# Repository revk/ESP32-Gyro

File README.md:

# ESP32-Gyro

Now at [Codeberg](https://codeberg.org/RevK/ESP32-Gyro)

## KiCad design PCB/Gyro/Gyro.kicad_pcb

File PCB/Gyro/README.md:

# Gyro

These files are for use in [KiCad](https://www.kicad.org).

## Trademark

This is an open source project, but bear in mind you cannot sell boards bearing the Andrews & Arnold Ltd name, the A&A logo, the registered trademark AJK logo, or the GS1 allocated EANs assigned to Andrews & Arnold Ltd.

## Images

*Auto generated 2025-07-08T09:44:21*

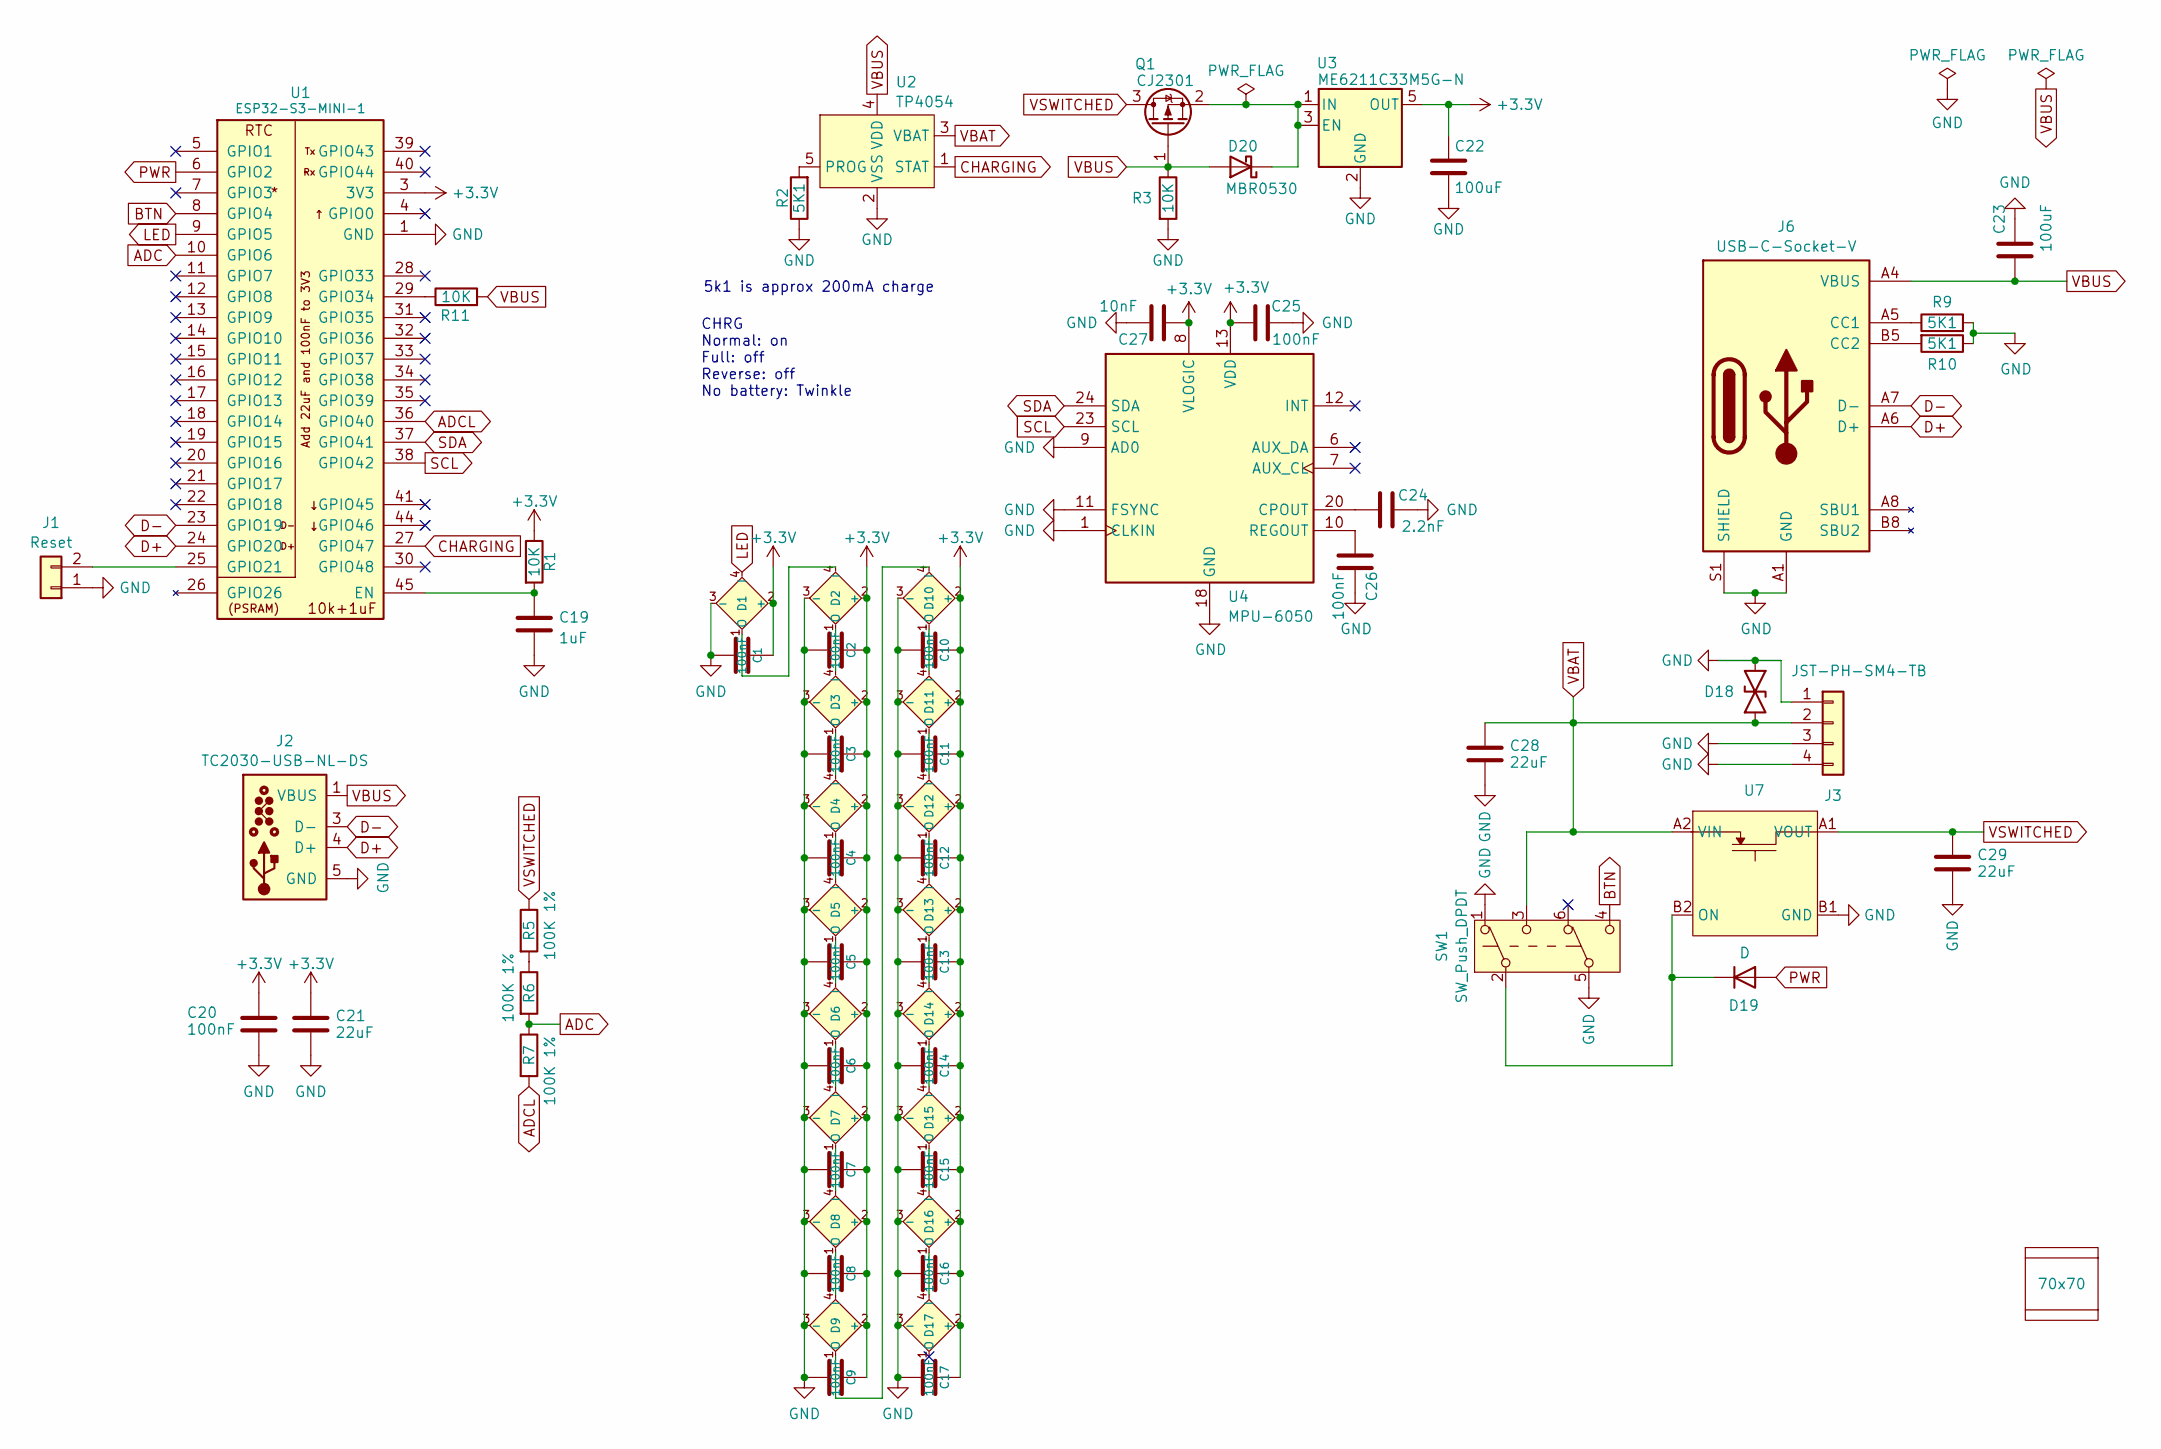
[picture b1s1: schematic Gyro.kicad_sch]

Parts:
C1, C2, C3, C4, C5, C6, C7, C8, C9, C10, C11, C12, C13, C14, C15, C16, C17, C20, C25, C26: 100nF; C_0402
C19: 1uF; C_0402
C21, C28, C29: 22uF; C_0603
C22, C23: 100uF; C_0805; MPN C141660
C24: 2.2nF; C_0402
C27: 10nF; C_0402
D1, D2, D3, D4, D5, D6, D7, D8, D9, D10, D11, D12, D13, D14, D15, D16, D17: XL-1010RGBC-WS2812B; SMD1010; MPN C5349953
D18: DFN1006-2L; MPN C5137770
D19: D; D_0402; MPN C28642302
D20: MBR0530; D_SOD-123; MPN C5204746
J1: Reset; AA-Pad
J2: TC2030-USB-NL-DS; Tag-Connect_TC2030-IDC-NL_2x03_P1.27mm_Vertical
J3: JST-PH-SM4-TB; JST_PH_S2B-PH-SM4-TB_1x02-1MP_P2.00mm_Horizontal; MPN C295747
J6: USB-C-Socket-V; USB-C-Socket-H; MPN C709357
PCB1: 70x70; PCB7070
Q1: CJ2301; SOT-23; MPN C8547
R1, R3, R11: 10K; R_0402; MPN C25744
R2, R9, R10: 5K1; R_0402; MPN C25905
R5, R6, R7: 100K 1%; R_0402; MPN C5139597
SW1: SW_Push_DPDT; MPN C2911139
U1: ESP32-S3-MINI-1; MPN C3013941
U2: TP4054; SOT-23-5; MPN C668215
U3: ME6211C33M5G-N; SOT-23-5; MPN C82942
U4: MPU-6050; InvenSense_QFN-24_4x4mm_P0.5mm; MPN C24112
U7: WCSP-4-0.78x0.78; MPN C2655476
V1, V2: VCUT70N

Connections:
+3.3V: C1.1, C2.1, C3.1, C4.1, C5.1, C6.1, C7.1, C8.1, C9.1, C10.1, C11.1, C12.1, C13.1, C14.1, C15.1, C16.1, C17.1, C20.1, C21.1, C22.1, C25.1, C27.1, D1.2 (+), D2.2 (+), D3.2 (+), D4.2 (+), D5.2 (+), D6.2 (+), D7.2 (+), D8.2 (+), D9.2 (+), D10.2 (+), D11.2 (+), D12.2 (+), D13.2 (+), D14.2 (+), D15.2 (+), D16.2 (+), D17.2 (+), R1.1, U1.3 (3V3), U3.5 (OUT), U4.8 (VLOGIC), U4.13 (VDD)
ADC: R6.2, R7.1, U1.10 (GPIO6)
ADCL: R7.2, U1.36 (GPIO40)
BTN: SW1.4 (C), U1.8 (GPIO4)
CHARGING: U1.27 (GPIO47), U2.1 (STAT)
D+: J2.4 (D+), J6.A6 (D+), J6.B6 (D+), U1.24 (GPIO20)
D-: J2.2 (NC), J2.3 (D-), J2.6 (NC), J6.A7 (D-), J6.B7 (D-), U1.23 (GPIO19)
GND: C1.2, C2.2, C3.2, C4.2, C5.2, C6.2, C7.2, C8.2, C9.2, C10.2, C11.2, C12.2, C13.2, C14.2, C15.2, C16.2, C17.2, C19.2, C20.2, C21.2, C22.2, C23.2, C24.2, C25.2, C26.2, C27.2, C28.2, C29.2, D1.3 (-), D2.3 (-), D3.3 (-), D4.3 (-), D5.3 (-), D6.3 (-), D7.3 (-), D8.3 (-), D9.3 (-), D10.3 (-), D11.3 (-), D12.3 (-), D13.3 (-), D14.3 (-), D15.3 (-), D16.3 (-), D17.3 (-), D18.1, J1.1, J2.5 (GND), J3.1, J3.3, J3.4, J6.A1 (GND), J6.A12 (GND), J6.B1 (GND), J6.B12 (GND), J6.S1 (SHIELD), R2.1, R3.2, R9.2, R10.1, SW1.1 (A), SW1.5 (B), U1.1 (GND), U1.2 (GND), U1.42 (GND), U1.43 (GND), U1.46 (GND), U1.47 (GND), U1.48 (GND), U1.49 (GND), U1.50 (GND), U1.51 (GND), U1.52 (GND), U1.53 (GND), U1.54 (GND), U1.55 (GND), U1.56 (GND), U1.57 (GND), U1.58 (GND), U1.59 (GND), U1.60 (GND), U1.61 (GND), U1.62 (GND), U1.63 (GND), U1.64 (GND), U1.65 (GND), U2.2 (VSS), U3.2 (GND), U4.1 (CLKIN), U4.9 (AD0), U4.11 (FSYNC), U4.18 (GND), U7.B1 (GND)
LED: D1.4 (I), U1.9 (GPIO5)
unnamed: D1.1 (O), D2.4 (I)
unnamed: D2.1 (O), D3.4 (I)
unnamed: D3.1 (O), D4.4 (I)
unnamed: D4.1 (O), D5.4 (I)
unnamed: D5.1 (O), D6.4 (I)
unnamed: D6.1 (O), D7.4 (I)
unnamed: D7.1 (O), D8.4 (I)
unnamed: D8.1 (O), D9.4 (I)
unnamed: D9.1 (O), D10.4 (I)
unnamed: D10.1 (O), D11.4 (I)
unnamed: D11.1 (O), D12.4 (I)
unnamed: D12.1 (O), D13.4 (I)
unnamed: D13.1 (O), D14.4 (I)
unnamed: D14.1 (O), D15.4 (I)
unnamed: D15.1 (O), D16.4 (I)
unnamed: D16.1 (O), D17.4 (I)
unnamed: D19.1 (K), SW1.2 (B), U7.B2 (ON)
unnamed: D20.1 (K), Q1.2 (S), U3.1 (IN), U3.3 (EN)
unnamed: J1.2, U1.25 (GPIO21)
unnamed: J6.A5 (CC1), R9.1
unnamed: J6.B5 (CC2), R10.2
unnamed: R5.2, R6.1
unnamed: C19.1, R1.2, U1.45 (EN)
unnamed: R11.1, U1.29 (GPIO34)
unnamed: R2.2, U2.5 (PROG)
unnamed: C24.1, U4.20 (CPOUT)
unnamed: C26.1, U4.10 (REGOUT)
PWR: D19.2 (A), U1.6 (GPIO2)
SCL: U1.38 (GPIO42), U4.23 (SCL)
SDA: U1.37 (GPIO41), U4.24 (SDA)
VBAT: C28.1, D18.2, J3.2, SW1.3 (C), U2.3 (VBAT), U7.A2 (VIN)
VBUS: C23.1, D20.2 (A), J2.1 (VBUS), J6.A4 (VBUS), J6.A9 (VBUS), J6.B4 (VBUS), J6.B9 (VBUS), Q1.1 (G), R3.1, R11.2, U2.4 (VDD)
VSWITCHED: C29.1, Q1.3 (D), R5.1, U7.A1 (VOUT)

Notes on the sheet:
5k1 is approx 200mA charge
CHRG Normal: on Full: off Reverse: off No battery: Twinkle

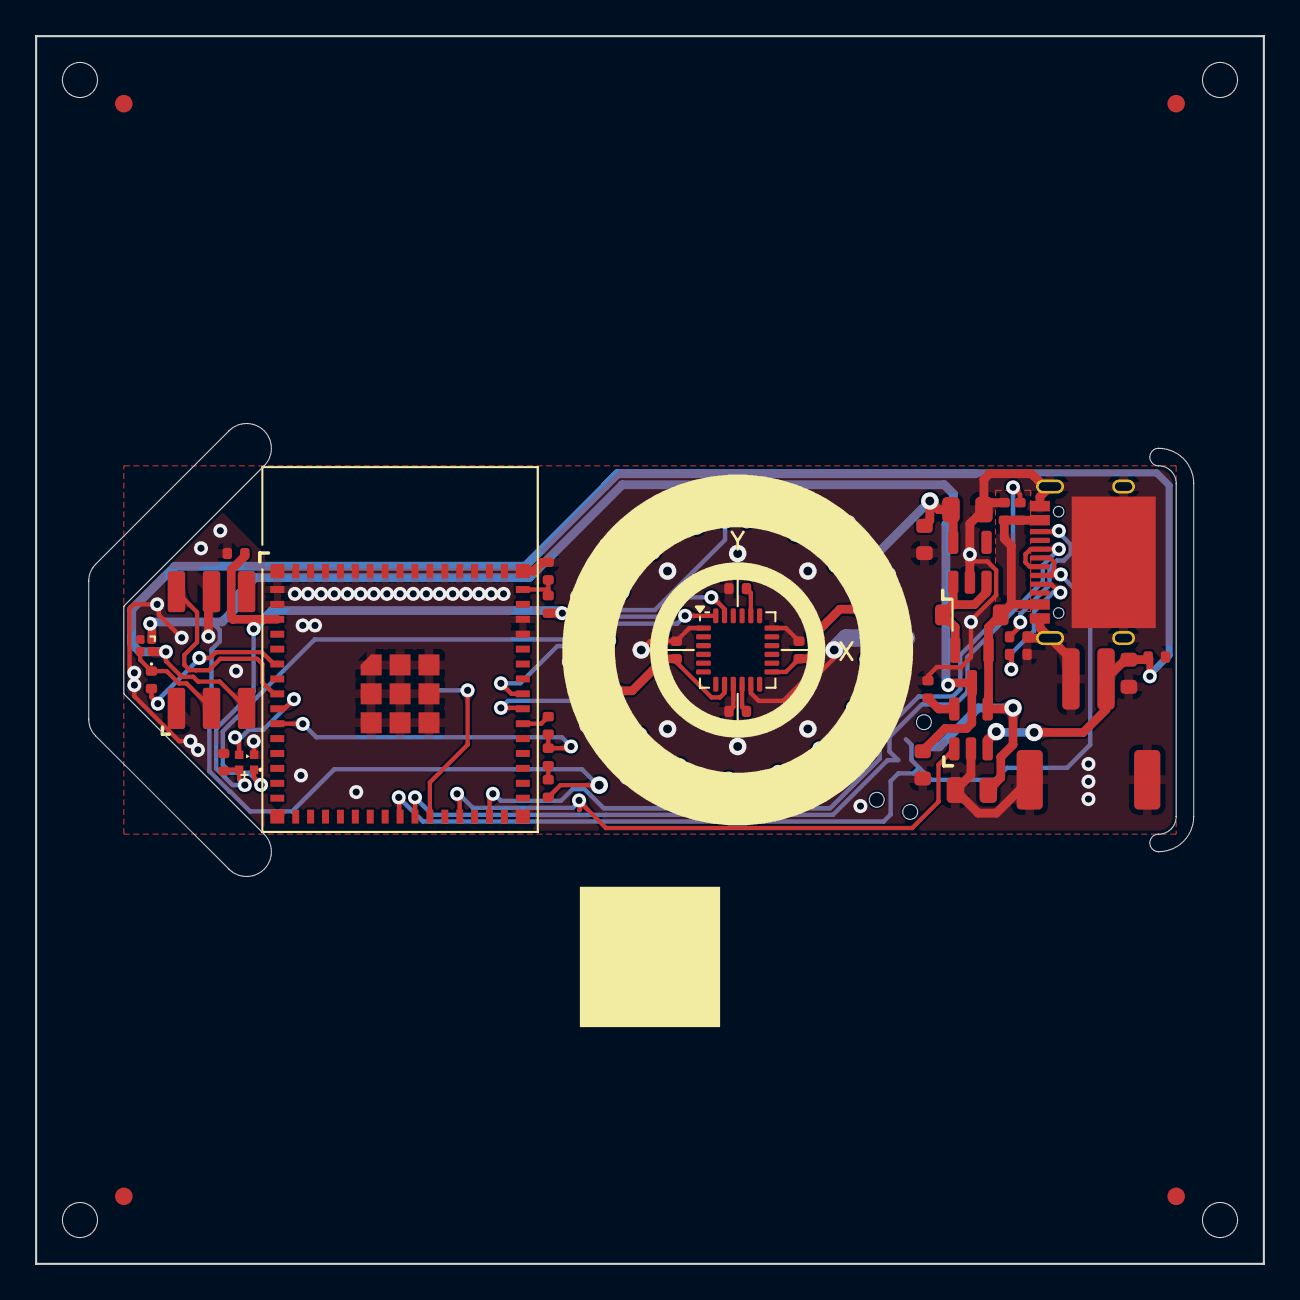
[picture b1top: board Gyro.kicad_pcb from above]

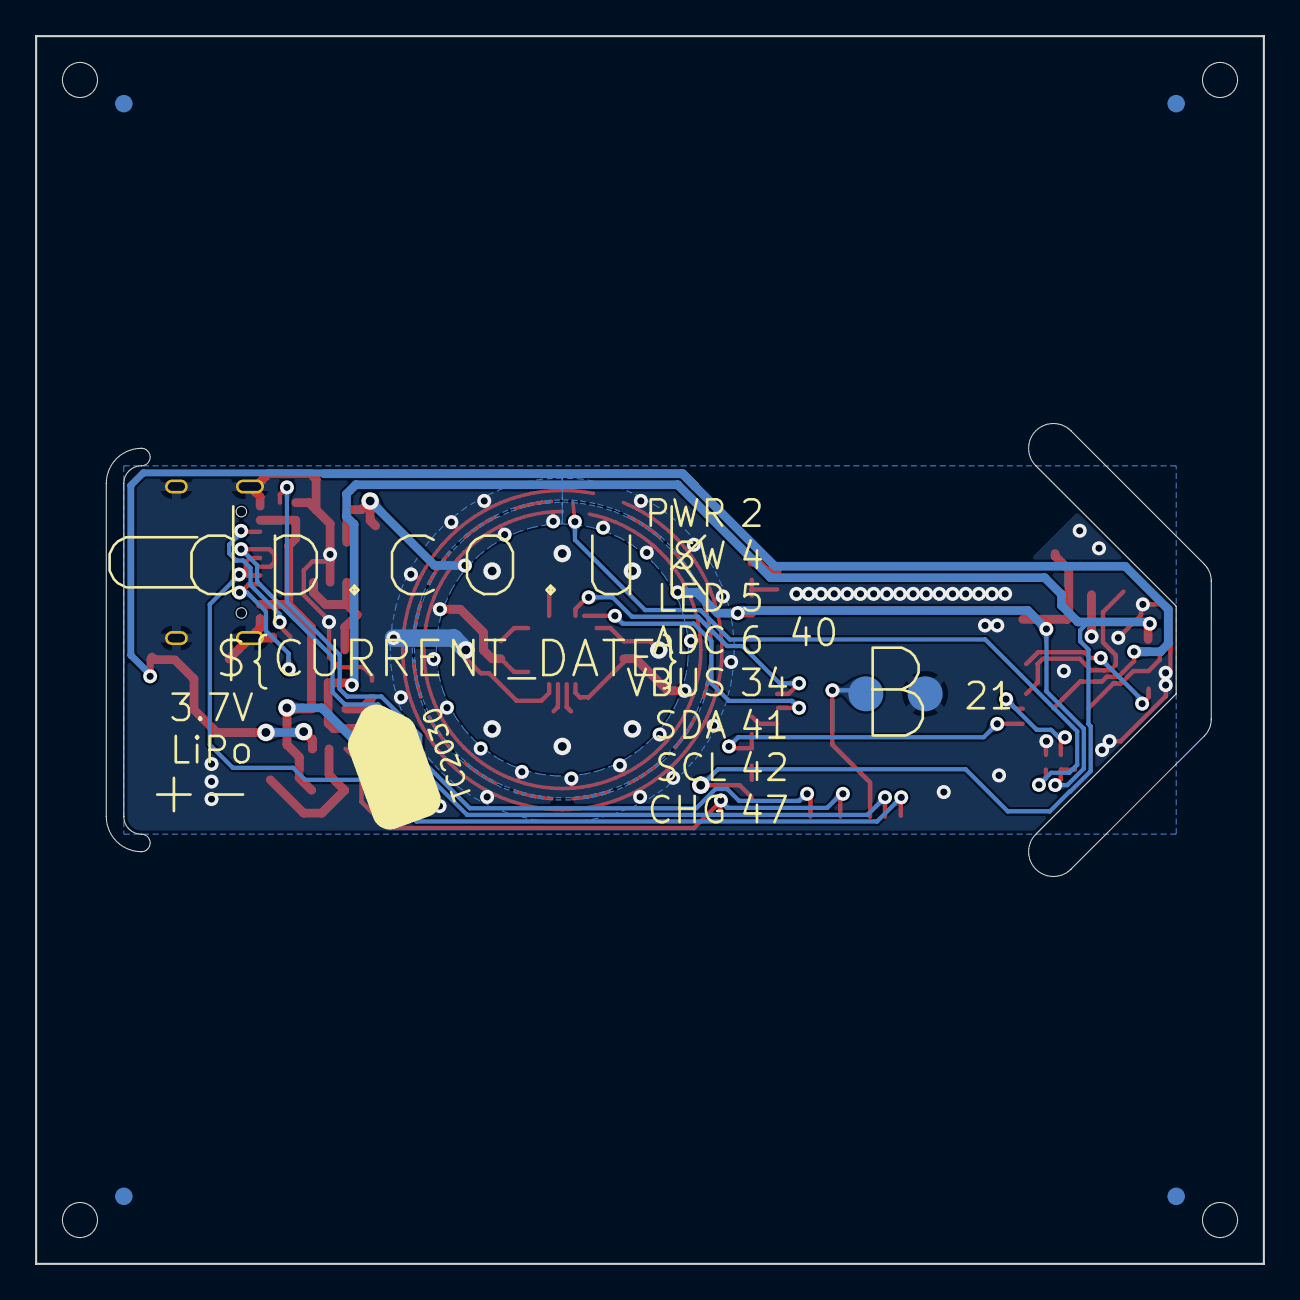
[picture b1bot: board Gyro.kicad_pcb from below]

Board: 2 copper layers, 70.0 x 70.0 mm, 71 parts (3 on the bottom side), 42 nets.

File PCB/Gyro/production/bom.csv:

Designator,Footprint,Quantity,Value,LCSC Part #
"C1, C10, C11, C12, C13, C14, C15, C16, C17, C2, C20, C3, C4, C5, C6, C7, C8, C9",C_0402,18,100nF,
C19,C_0402,1,1uF,
"C21, C28, C29",C_0603,3,22uF,
"C22, C23",C_0805,2,100uF,C141660
C24,C_0402,1,2.2nF,
"C25, C26",C_0402,2,100nF,
C27,C_0402,1,10nF,
"D1, D10, D11, D12, D13, D14, D15, D16, D17, D2, D3, D4, D5, D6, D7, D8, D9",SMD1010,17,XL-1010RGBC-WS2812B,C5349953
D18,DFN1006-2L,1,~,C5137770
D19,D_0402,1,D,C28642302
D20,D_SOD-123,1,MBR0530,C5204746
J3,JST_PH_S2B-PH-SM4-TB_1x02-1MP_P2.00mm_Horizontal,1,JST-PH-SM4-TB,C295747
J6,USB-C-Socket-H,1,USB-C-Socket-V,C709357
Q1,SOT-23,1,CJ2301,C8547
"R1, R11, R3",R_0402,3,10K,C25744
"R10, R2, R9",R_0402,3,5K1,C25905
"R5, R6, R7",R_0402,3,100K 1%,C5139597
SW1,SW_Push_DPDT,1,SW_Push_DPDT,C2911139
U1,ESP32-S3-MINI-1,1,ESP32-S3-MINI-1,C3013941
U2,SOT-23-5,1,TP4054,C668215
U3,SOT-23-5,1,ME6211C33M5G-N,C82942
U4,InvenSense_QFN-24_4x4mm_P0.5mm,1,MPU-6050,C24112
U7,WCSP-4-0.78x0.78,1,~,C2655476

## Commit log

2025-06-17 Started PCb
2025-06-17 Tidy
2025-06-17 Started
2025-06-17 As ordered
2025-06-17 Slioght tidy
2025-06-18 V-cuts fix
2025-06-20 ADCL
2025-06-21 Try the power distribution switches.
2025-06-22 Tweaks
2025-06-22 Tweak SS
2025-06-24 Tweak
2025-06-25 Library update
2025-06-25 Still wont build?!
2025-06-25 FFS not working
2025-06-25 I fucking hate CMake
2025-06-25 Basic null app
2025-06-25 null app issue
2025-06-25 test
2025-06-25 Some data
2025-06-26 Basic working
2025-06-26 Basic level on LEDs
2025-06-26 More level
2025-06-26 Progress
2025-06-26 Comments
2025-06-26 FIFO fix
2025-06-26 Fade for low G
2025-06-26 Cleaner spirit level
2025-06-28 Beta
2025-06-28 Release
2025-06-29 Battery and button
2025-06-29 Tweak blue
2025-06-29 general status
2025-06-29 New board
2025-06-30 Adjust battery and report G
2025-06-30 Cleaner buttoin handling
2025-06-30 power off MPU-6050
2025-06-30 Bat cal
2025-06-30 3.1V base
2025-07-02 comment
2025-07-07 New boards
2025-07-08 Power off
2025-07-08 power
2025-07-08 New power control
2025-07-08 Render
2025-07-27 Moving averages
2026-02-13 submodule
2026-02-15 Codeberg
